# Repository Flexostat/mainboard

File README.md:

# mainboard
The main PCB that runs the Flexostat

<br />This work is licensed under a <a rel="license" href="http://creativecommons.org/licenses/by/4.0/">Creative Commons Attribution 4.0 International License</a>.

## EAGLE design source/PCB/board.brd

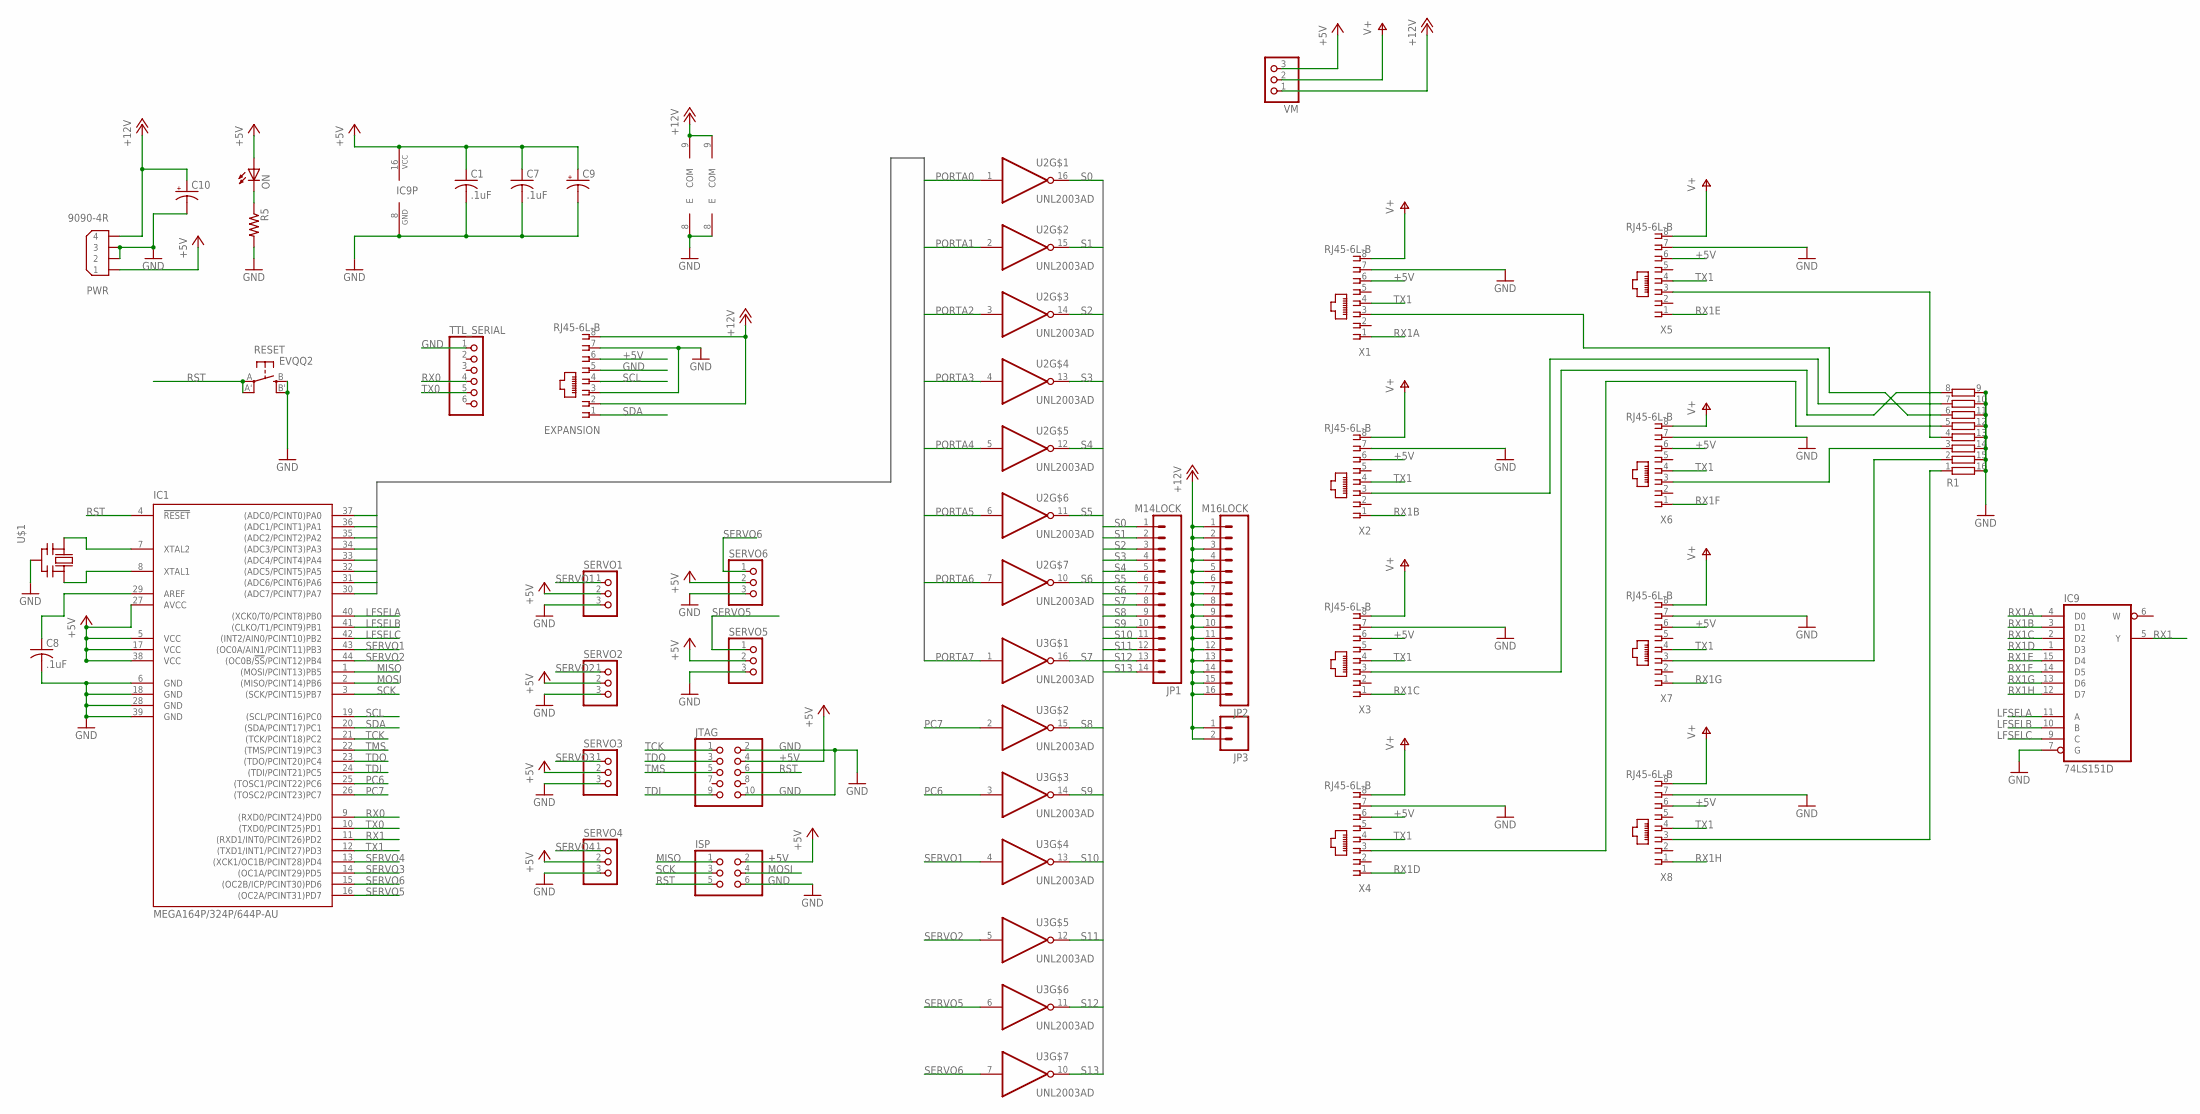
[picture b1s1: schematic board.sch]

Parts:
C1, C7, C8: .1uF; C0805
C9, C10: CPOL-USE2.5-7; E2,5-7
EXPANSION: RJ45-6L-B; RJ45-NO-SHIELD
IC1: MEGA164P/324P/644P-AU; TQFP44
IC9: 74LS151D; SO16
ISP: PINHD-2X3; 2X03
JP1: M14LOCK; 1X14_LOCK
JP2: M16LOCK; 1X16_LOCK
JP3: M02PTH; 1X02
JTAG: PINHD-2X5; 2X05
ON: LEDCHIPLED_0805; CHIPLED_0805
PWR: 9090-4R
R1: 2NBS16-8; SO16
R5: R-US_R0805; R0805
RESET: EVQQ2; EVQ-Q2
SERVO1, SERVO2, SERVO3, SERVO4, SERVO5, SERVO6: PINHD-1X3; 1X03
TTL_SERIAL: PINHD-1X6; 1X06
U2, U3: UNL2003AD; SO16
U$1: CERMOSCILL-CSTCRG; CSTCR-G
VM: PINHD-1X3; 1X03
X1, X2, X3, X4, X5, X6, X7, X8: RJ45-6L-B; RJ45-NO-SHIELD

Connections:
+5V: C1.1, C7.1, C9.+, EXPANSION.6, IC1.5 (VCC), IC1.17 (VCC), IC1.27 (AVCC), IC1.38 (VCC), IC9.16 (VCC), ISP.2, JTAG.4, ON.A, PWR.1, SERVO1.2, SERVO2.2, SERVO3.2, SERVO4.2, SERVO5.2, SERVO6.2, VM.3, X1.6, X2.6, X3.6, X4.6, X5.6, X6.6, X7.6, X8.6
+12V: C10.+, EXPANSION.2, EXPANSION.8, JP2.1, JP2.2, JP2.3, JP2.4, JP2.5, JP2.6, JP2.7, JP2.8, JP2.9, JP2.10, JP2.11, JP2.12, JP2.13, JP2.14, JP2.15, JP2.16, JP3.1, JP3.2, PWR.4, U2.9 (COM), U3.9 (COM), VM.1
GND: C1.2, C7.2, C8.2, C9.-, C10.-, EXPANSION.3, EXPANSION.5, EXPANSION.7, IC1.6 (GND), IC1.18 (GND), IC1.28 (GND), IC1.39 (GND), IC9.7 (G), IC9.8 (GND), ISP.6, JTAG.2, JTAG.10, PWR.2, PWR.3, R1.9, R1.10, R1.11, R1.12, R1.13, R1.14, R1.15, R1.16, R5.2, RESET.B (S), RESET.B' (S1), SERVO1.3, SERVO2.3, SERVO3.3, SERVO4.3, SERVO5.3, SERVO6.3, TTL_SERIAL.1, U2.8 (E), U3.8 (E), U$1.2 (GND), X1.7, X2.7, X3.7, X4.7, X5.7, X6.7, X7.7, X8.7
LFSELA: IC1.40 ((XCK0/T0/PCINT8)PB0), IC9.11 (A)
LFSELB: IC1.41 ((CLKO/T1/PCINT9)PB1), IC9.10 (B)
LFSELC: IC1.42 ((INT2/AIN0/PCINT10)PB2), IC9.9 (C)
MISO: IC1.1 ((MOSI/PCINT13)PB5), ISP.1
MOSI: IC1.2 ((MISO/PCINT14)PB6), ISP.4
unnamed: IC1.7 (XTAL2), U$1.1 (IN)
unnamed: IC1.8 (XTAL1), U$1.3 (OUT)
unnamed: R1.1, X8.3
unnamed: R1.6, X1.3
unnamed: R1.7, X2.3
unnamed: R1.8, X3.3
unnamed: R1.5, X4.3
unnamed: R1.4, X5.3
unnamed: R1.3, X6.3
unnamed: R1.2, X7.3
unnamed: C8.1, IC1.29 (AREF)
unnamed: ON.C, R5.1
PC6: IC1.25 ((TOSC1/PCINT22)PC6), U3.3 (I)
PC7: IC1.26 ((TOSC2/PCINT23)PC7), U3.2 (I)
PORTA0: IC1.37 ((ADC0/PCINT0)PA0), U2.1 (I)
PORTA1: IC1.36 ((ADC1/PCINT1)PA1), U2.2 (I)
PORTA2: IC1.35 ((ADC2/PCINT2)PA2), U2.3 (I)
PORTA3: IC1.34 ((ADC3/PCINT3)PA3), U2.4 (I)
PORTA4: IC1.33 ((ADC4/PCINT4)PA4), U2.5 (I)
PORTA5: IC1.32 ((ADC5/PCINT5)PA5), U2.6 (I)
PORTA6: IC1.31 ((ADC6/PCINT6)PA6), U2.7 (I)
PORTA7: IC1.30 ((ADC7/PCINT7)PA7), U3.1 (I)
RST: IC1.4 (!RESET), ISP.5, JTAG.6, RESET.A, RESET.A' (P1)
RX0: IC1.9 ((RXD0/PCINT24)PD0), TTL_SERIAL.4
RX1: IC1.11 ((RXD1/INT0/PCINT26)PD2), IC9.5 (Y)
RX1A: IC9.4 (D0), X1.1
RX1B: IC9.3 (D1), X2.1
RX1C: IC9.2 (D2), X3.1
RX1D: IC9.1 (D3), X4.1
RX1E: IC9.15 (D4), X5.1
RX1F: IC9.14 (D5), X6.1
RX1G: IC9.13 (D6), X7.1
RX1H: IC9.12 (D7), X8.1
S0: JP1.1, U2.16 (O)
S1: JP1.2, U2.15 (O)
S2: JP1.3, U2.14 (O)
S3: JP1.4, U2.13 (O)
S4: JP1.5, U2.12 (O)
S5: JP1.6, U2.11 (O)
S6: JP1.7, U2.10 (O)
S7: JP1.8, U3.16 (O)
S8: JP1.9, U3.15 (O)
S9: JP1.10, U3.14 (O)
S10: JP1.11, U3.13 (O)
S11: JP1.12, U3.12 (O)
S12: JP1.13, U3.11 (O)
S13: JP1.14, U3.10 (O)
SCK: IC1.3 ((SCK/PCINT15)PB7), ISP.3
SCL: EXPANSION.4, IC1.19 ((SCL/PCINT16)PC0)
SDA: EXPANSION.1, IC1.20 ((SDA/PCINT17)PC1)
SERVO1: IC1.43 ((OC0A/AIN1/PCINT11)PB3), SERVO1.1, U3.4 (I)
SERVO2: IC1.44 ((OC0B/!SS!/PCINT12)PB4), SERVO2.1, U3.5 (I)
SERVO3: IC1.14 ((OC1A/PCINT29)PD5), SERVO3.1
SERVO4: IC1.13 ((XCK1/OC1B/PCINT28)PD4), SERVO4.1
SERVO5: IC1.16 ((OC2A/PCINT31)PD7), SERVO5.1, U3.6 (I)
SERVO6: IC1.15 ((OC2B/ICP/PCINT30)PD6), SERVO6.1, U3.7 (I)
TCK: IC1.21 ((TCK/PCINT18)PC2), JTAG.1
TDI: IC1.24 ((TDI/PCINT21)PC5), JTAG.9
TDO: IC1.23 ((TDO/PCINT20)PC4), JTAG.3
TMS: IC1.22 ((TMS/PCINT19)PC3), JTAG.5
TX0: IC1.10 ((TXD0/PCINT25)PD1), TTL_SERIAL.5
TX1: IC1.12 ((TXD1/INT1/PCINT27)PD3), X1.4, X2.4, X3.4, X4.4, X5.4, X6.4, X7.4, X8.4
V+: VM.2, X1.8, X2.8, X3.8, X4.8, X5.8, X6.8, X7.8, X8.8

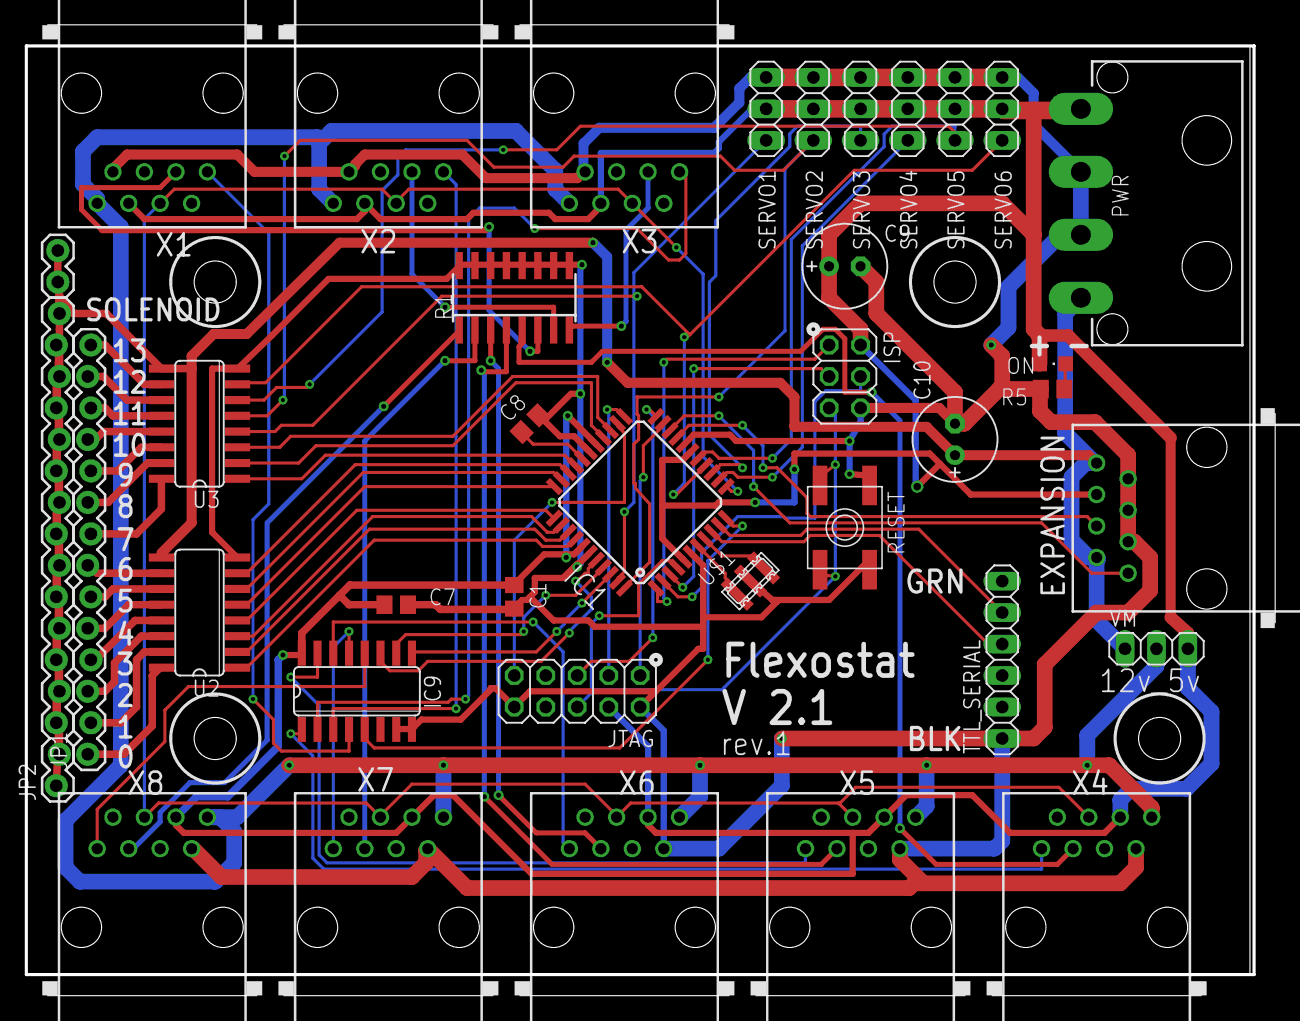
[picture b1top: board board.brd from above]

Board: 2 copper layers, 100.6 x 78.1 mm, 37 parts (0 on the bottom side), 71 nets.

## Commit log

2012-11-03 First commit of turbidostat 1.0 hardware and firmware files
2013-03-06 added firmware code
2014-05-13 updated directory structure and added binaries
2014-08-08 added git ignore
2014-08-08 updated gitignore
2014-08-13 code update for mainboard v2.0
2014-11-18 Added SPV pulse functionality for syphoning media.--ONLY COMPATIBLE WITH NEWEST MAINBOARD LABELED 'FLEXOSTAT V2.0'--
2014-11-18 udptade to FLEXOSTAT V2.0
2014-11-18 fixed overlay layer. SPV numbers now line up with pins
2015-04-14 small firmware but where chamber 8 wouldn't close under some circumstances
2015-04-14 updated binaries. added production file
2015-04-17 basic i2c support
2015-04-17 i2c PV support
2016-01-24 v2.1 files
2016-02-11 updated design with mounting holes and wider traces
2016-02-11 git ignore added
2017-11-15 clean up and refactor
2020-03-09 added CCBY

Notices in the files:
parts and their libraries:
SparkFun-Connectors: Licensing: CC v3.0 Share-Alike You are welcome to use this library for commercial purposes.
